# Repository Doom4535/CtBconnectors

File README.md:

# CtBconnectors
Assorted collection of cable to breadboard breakout schematics

This is a random grouping of breakout boards for some common cable types.
It was inspired by my need for a ribbon cable to breadboard adapter and has
since grown to include a variety of different connectors.

Included connectors: <br />
  * SATA power <br />
  * SATA Data <br />
  * 8x ribbon <br />
  * 10x ribbon <br />
  * 16x ribbon <br />
  * 20x ribbon <br />
  * 40x ribbon <br />
  * 46x ribbon <br />
  * RJ11 (Phone jack) <br />
  * RJ45 (Ethernet jack) <br />
  
Currently, all the modules are in a single project file.  I may or may not split
them out into their own independent batch of gerber files (for easier custom panelization).
The current grouping was chosen to speed up layout and because I use low cost fab houses
(such as DirtyPCB, OshPark, PCBway, and Elecrow) that send you 'x' number of PCB's with each order,
and I would like to have a variety of connectors (hence the 'variety' pack).

Use: https://github.com/ThisIsNotRocketScience/GerberTools to combine into a single panel if desired

Change .gm1 to .gko
The drill file with the .txt output seems to be the non-plated drill file
and the file with the .drl extension seems to be the NC drill file.  Dirty PCB seems to distinguish between them based on the rendering even though the file list ignores the *.drl file.
Renamed the .drl to *-PTH.drl and changed the .txt to *-NPTH.txt

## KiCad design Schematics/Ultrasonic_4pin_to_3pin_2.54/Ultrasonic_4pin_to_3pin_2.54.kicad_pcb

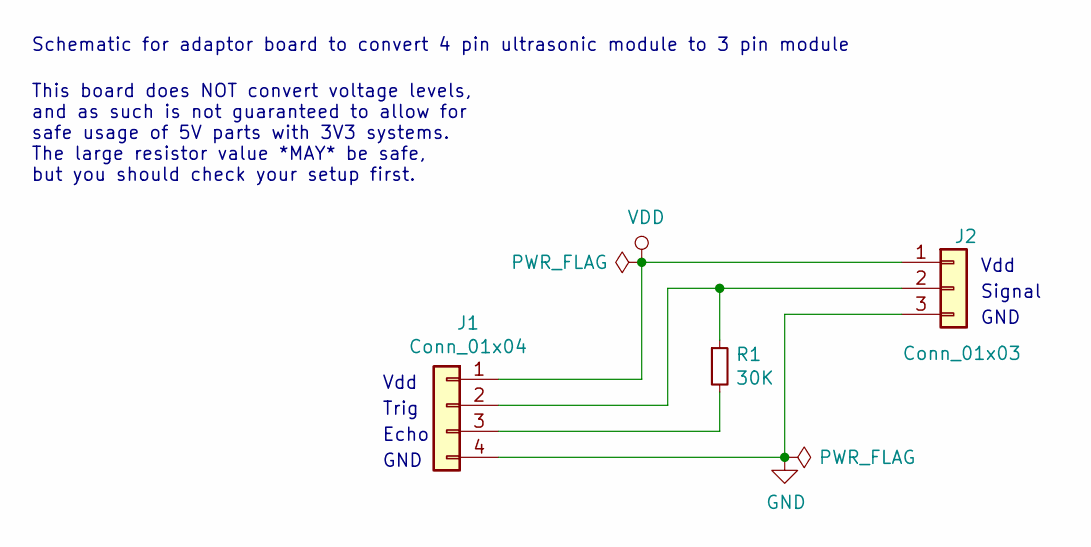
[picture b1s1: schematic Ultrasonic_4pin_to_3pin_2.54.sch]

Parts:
J1: Conn_01x04; PinSocket_1x04_P2.54mm_Horizontal
J2: Conn_01x03; PinHeader_1x03_P2.54mm_Horizontal
R1: 30K; R_0402_1005Metric

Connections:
GND: J1.4, J2.3
unnamed: J1.2, J2.2, R1.1
unnamed: J1.3, R1.2
VDD: J1.1, J2.1

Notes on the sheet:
Vdd
Trig
Echo
GND
Signal
Schematic for adaptor board to convert 4 pin ultrasonic module to 3 pin module
This board does NOT convert voltage levels, and as such is not guaranteed to allow for safe usage of 5V parts with 3V3 systems. The large resistor value *MAY* be safe, but you should check your setup first.

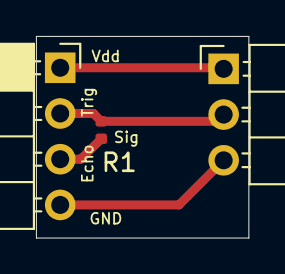
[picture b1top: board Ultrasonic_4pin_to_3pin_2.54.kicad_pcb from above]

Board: 2 copper layers, 11.8 x 11.2 mm, 3 parts (0 on the bottom side), 4 nets.

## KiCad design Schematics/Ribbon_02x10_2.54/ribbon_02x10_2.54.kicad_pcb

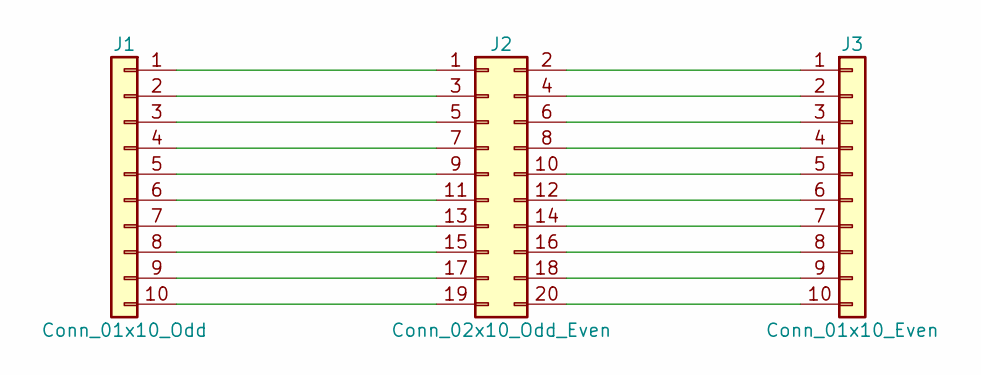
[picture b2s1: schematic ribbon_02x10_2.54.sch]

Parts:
J1: Conn_01x10_Odd; Pin_Header_Straight_1x10_Pitch2.54mm_SMD_Pin1Right
J2: Conn_02x10_Odd_Even; Pin_Header_Straight_2x10_Pitch2.54mm_SMD
J3: Conn_01x10_Even; Pin_Header_Straight_1x10_Pitch2.54mm_SMD_Pin1Right

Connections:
unnamed: J1.1, J2.1
unnamed: J1.2, J2.3
unnamed: J1.3, J2.5
unnamed: J1.4, J2.7
unnamed: J1.5, J2.9
unnamed: J1.6, J2.11
unnamed: J1.7, J2.13
unnamed: J1.8, J2.15
unnamed: J1.9, J2.17
unnamed: J1.10, J2.19
unnamed: J2.2, J3.1
unnamed: J2.4, J3.2
unnamed: J2.6, J3.3
unnamed: J2.8, J3.4
unnamed: J2.10, J3.5
unnamed: J2.12, J3.6
unnamed: J2.14, J3.7
unnamed: J2.16, J3.8
unnamed: J2.18, J3.9
unnamed: J2.20, J3.10

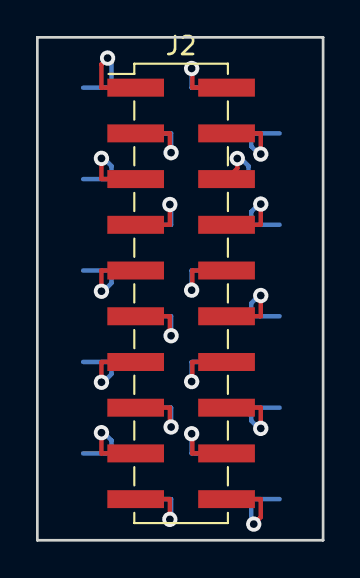
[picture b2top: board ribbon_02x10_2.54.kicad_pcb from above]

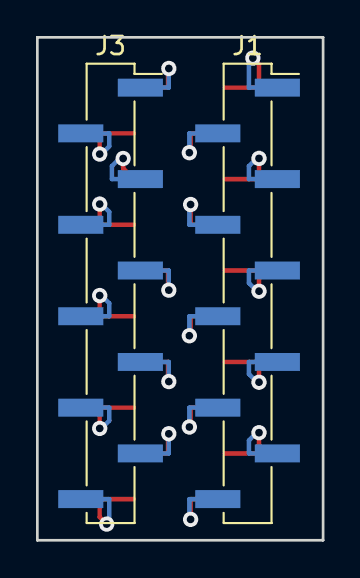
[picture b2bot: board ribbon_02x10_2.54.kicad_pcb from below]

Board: 2 copper layers, 15.9 x 27.9 mm, 3 parts (2 on the bottom side), 20 nets.

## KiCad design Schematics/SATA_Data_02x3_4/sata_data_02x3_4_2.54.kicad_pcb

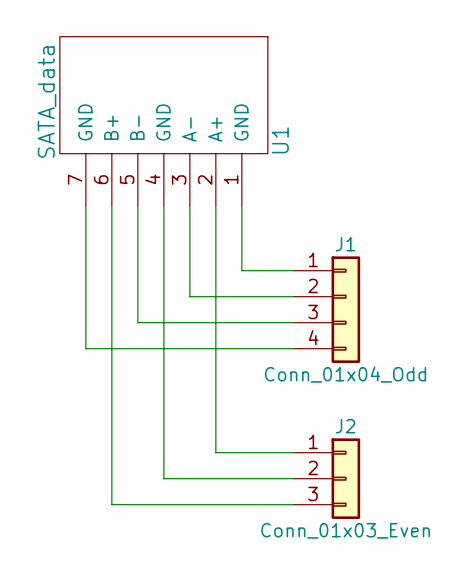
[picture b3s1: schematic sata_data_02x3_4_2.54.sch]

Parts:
J1: Conn_01x04_Odd; Pin_Header_Straight_1x04_Pitch2.54mm_SMD_Pin1Right
J2: Conn_01x03_Even; Pin_Header_Straight_1x03_Pitch2.54mm_SMD_Pin1Right
U1: SATA_data; SATA-7_SMD

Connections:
unnamed: J1.1, U1.1 (GND)
unnamed: J1.2, U1.3 (A-)
unnamed: J1.3, U1.5 (B-)
unnamed: J1.4, U1.7 (GND)
unnamed: J2.1, U1.2 (A+)
unnamed: J2.2, U1.4 (GND)
unnamed: J2.3, U1.6 (B+)

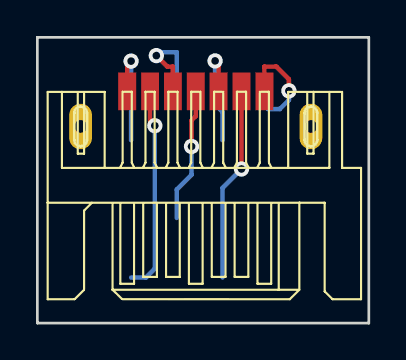
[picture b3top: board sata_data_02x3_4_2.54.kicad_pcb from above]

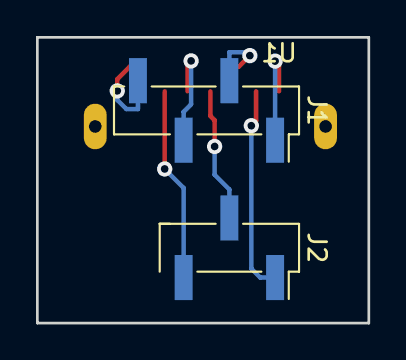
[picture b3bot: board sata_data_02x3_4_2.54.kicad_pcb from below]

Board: 2 copper layers, 18.4 x 15.9 mm, 3 parts (2 on the bottom side), 7 nets.

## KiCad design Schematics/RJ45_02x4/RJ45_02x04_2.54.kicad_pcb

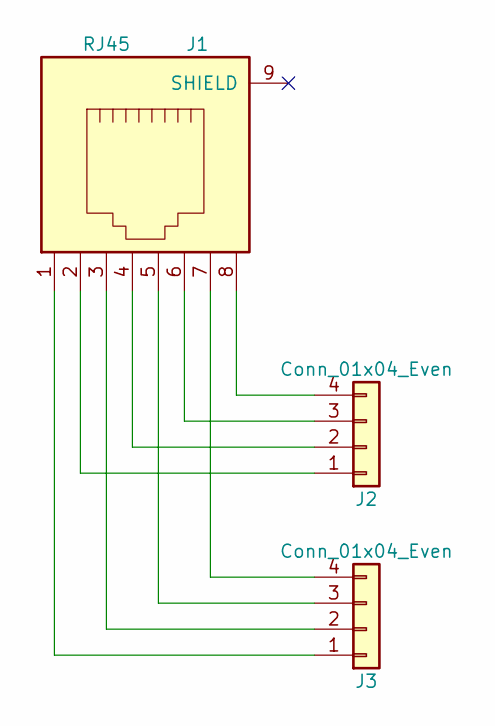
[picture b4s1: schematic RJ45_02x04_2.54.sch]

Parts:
J1: RJ45; RJ45_8
J2, J3: Conn_01x04_Even; Pin_Header_Straight_1x04_Pitch2.54mm_SMD_Pin1Right

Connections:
unnamed: J1.1, J3.1
unnamed: J1.2, J2.1
unnamed: J1.3, J3.2
unnamed: J1.4, J2.2
unnamed: J1.5, J3.3
unnamed: J1.6, J2.3
unnamed: J1.7, J3.4
unnamed: J1.8, J2.4

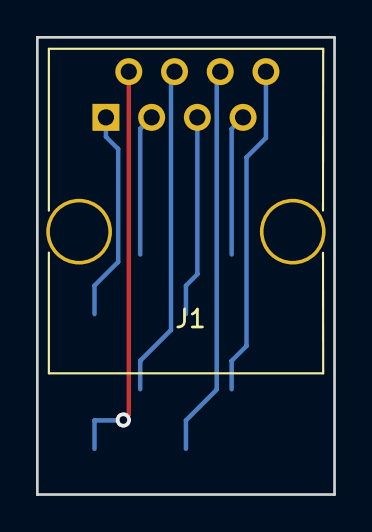
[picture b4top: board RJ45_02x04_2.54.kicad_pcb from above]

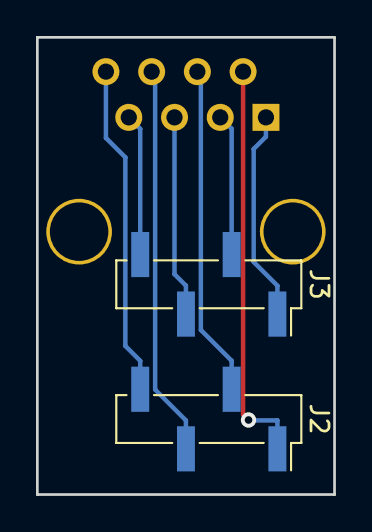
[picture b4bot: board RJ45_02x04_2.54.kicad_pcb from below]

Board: 2 copper layers, 16.5 x 25.4 mm, 3 parts (2 on the bottom side), 8 nets.

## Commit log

2017-12-29 Initial commit (incomplete)
2017-12-29 Caching progress, last ribbon set to link then start layout
2017-12-29 Update README.md
    Fixing readme line endings for webview
2017-12-29 Update README.md
    more readme edits...
2017-12-30 Modifying schematic organization
2018-01-02 Version 0.1 PCB
    Need to put cutouts and shrink some designs
2018-01-02 Modifying layout
    Shrank some layout area, now need to add cutouts
2018-01-02 Begining edge cuts
2018-01-03 Preparing for fab.
2018-01-03 Fixing via sizing issues
2018-01-03 Caching partial fix
2018-01-03 Removing outline, leaving mouse bites
2018-01-03 Removed several mouse bites, fixing 3d render
2018-01-03 Changing to using seperate projects for each header, should work better for pannelizing This is kinda annoying in that it does cause a lot of *.prj files to be used...
2018-01-15 Reworking to use seperate projects for each connector Merging the individual component gerbers into a single panelized gerber using gerber tools
2019-05-23 Added in 2 PicoBlade to 2.54 mm header boards These have not been included in the variety pack
2019-06-13 Fixing PicoBlade header direction issue Flipped the PicoBlade SMD header so that it doesn't point towards the through hole 2.54mm pin header
2019-06-13 Flipping board side, adding additional traces Extra/duplicate traces are to help 'self document' (so the user can see where each pin goes without viewing the schematic).
2019-06-13 Fixing missing change to schematic
2019-08-16 Updating picoblade footprint Now uses a footprint with mounting holes
2019-08-16 Updated PicoBlade 01x04 footprint Footprint now supports using mounting points (and PicoBlade is fully SMD)
2019-08-16 Fixing traces
2019-08-16 Updating PicoBlade 01x06 traces
2019-11-10 Adding an adapter for use with ultrasonic sensors This is a simple board that is intended to have a female socket on one side and a male pin header on the other to combine the Vtrig and Vecho pins th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
2019-11-11 Updated design Changed to use a 30K resistor (may allow for 5V to 3V3 logic), will provide better protection against driving the 'Echo' output with the 'Trig' signal. Changed PCB board sizing; if tri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
